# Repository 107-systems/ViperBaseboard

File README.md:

ViperBaseboard
==============

<p align="center">
  
</p>

This repository contains the requirements and the hardware design for MKR Vidor 4000 based Viper quadcopter.

## Quadcopter renderings

## PCB renderings

The **Viper Baseboard** serves as an adapter board between an Arduino MKR Vidor 4000 and various sensors and actuators in order to implement a flight controller for a quadcopter UAV.

The block diagramm has been created using [Ipe](http://ipe.otfried.org/) which can be installed via `sudo apt-get install ipe texlive-full` or `sudo apt-get install ipe texlive-base texlive-latex-recommended` for minimal installation).

## Requirements
### Functional Requirements
#### Rotational/Translational Stabilisation
The quadcopter should be able to stabilise itself against external disturbances concerning its orientation and position with respect to a given setpoint. For determining the current orientation of the quadcopter a suitable Inertial Measurement Unit (IMU) with a suitable sensor fusion algorithm shall be used. For determining translational stabilisation a optical flow sensor consisting of a downward facing camera in combination with a suitable optical flow sensor algorithm shall be used.

#### Vertical (Height) Stabilisation
The quadcopter should be able to hold a set distance over ground. In close proximity to the ground VL53L0X ToF sensors are used to  determine the distance between ground and quadcopter and prevent an accidential crash. When the distance between quadcopter and ground exceeds the maximum measurement range of the ground sensors the height will be controlled using a digital altimeter such as the BMP388.

#### WiFi based Control/Configuration
The quadcopter shall provide a WiFi access point to which a WiFi capable device can connect. Once a WiFi connection is established the quadcopter can be controlled via commands exchanged between quadcopter and device via a network socket. A webserver will run on the quadcopter which allows the user to configure and tweak certain aspects of the quadcopter configuration (e.g. control parameters) or read out quadcopter status.

#### Automonous Landing
The quadcopter should be able to land without user control. Three VL53L0X ToF sensors arranged in a triangle are used to determine the distance between ground and quadcopter and also perform an estimation of the grounds surface.

#### FPV (First-Person-View) Control
The image stream of a forward facing camera (a MIPI connector intented for use with the Omnivision OV5647 camera is available on the MKR VIDOR 4000 board) should be suitably encoded (in the FPGA) and transmitted via WiFi module in such way that a user can be view the image stream e.g. on a mobile phone which allows a FPV control of the quadcopter.\
It should be posible to switch the FPV from forward facing camera to ground facing camera and back. Then the user can choose which camera fits best his needs.

#### SD Card Storage
There should be a socket for a SD card on the baseboard. The flight controller then can log information like position or altitude or store video clips of the cameras or do image generation like map creation with the ground facing camera.

### Sensors
#### VL53L0X
The VL53L0X ToF Sensor allows a measurement range of up to 2 m with a resolution of 1 mm.\
**Attention:** all VL53L0X come up with the same I2C address. So we need additional circuitry to disable them with the XSHUT pin und give them individual addresses one after another.
#### BMP388
The BMP388 is a precision barometric pressure sensor wich relative accuracy of 8 Pascals, which translates to about ± 0.5 meter of altitude.
#### BNO085
The BNO085 contains 3 axis accelerometers, gyroscopes and magnetometers incl. onboard-algorithms for sensor fusion.
#### CD-PA1010D (Optional)
The [CD-PA1010D](doc/datasheet/Sensor-GPS-CD-PA1010D-v-0-3.pdf) is global positioning sensor supporting GPS, GLONASS, GALILEO, QZSS which can be interfaced both via UART and I2C.

### Actuators
#### Zubax Orel 20 ESCs
[Zubax Orel 20](https://kb.zubax.com/display/MAINKB/Zubax+Orel+20) are used as ESC (Electronic Speed Controllers) and controlled via [UAVCAN](https://uavcan.org).

### Electrical Requirements

* **Input Voltage**: 9 - 18.5 V (same as the Zubax Orel 20).
* **Input Protection**: Input voltage should be protected by a TVS diode against voltage spikes from the motors.
There is no fuse because the motor drivers can draw excessive currents. Then a fuse is useless because it should have a very high current rating and then it can'tprotect very much. Additionally the fuse would add additional weight and empose a risk of failure during flight.

#### Power planes and distribution
* **Input Voltage**: to motor drivers and input for voltage regulators, current: 20 to 30 A.
* **5V**:
Input for Arduino because the Arduino doesn't like to be directly fed with 3.3V.
generated on by a switching regulator.
Current: 500 mA + Current for 3.3V devices
* **3.3V**:
for sensors and camera module
generated by the onboard regulator of the Arduino
Current: up to 100 mA, should be OK for the onboard regulator

#### Connectors (mechanical and pinout)
##### Battery / Input
##### CAN
The Zubax Orel 20 ESCs utilize the [JST GH](http://www.jst-mfg.com/product/detail_e.php?series=105) connectors with a pitch of 1.25 mm.

| **Pin** | **Signal** |
|:-------:|:----------:|
| 1       | VCC        |
| 2       | CAN_H      |
| 3       | CAN_L      |
| 4       | GND        |

#### Connections of Arduino MKR Vidor 4000

* **MKR connector** (2.54 mm pinheader, 28 pins)
  * I2C
  * CAN over SPI (like on MKRCANShield)
  * 5V input, 3.3V output
  * RC_IN (for additional remote control receiver)

| **Pin** | **Pin Name** | **Signal**    | **Description**                |
|:-------:|:------------:|:-------------:|:------------------------------:|
| 1       | AREF         | not connected |                                |
| 2       | DAC0/A0      |               |                                |
| 3       | A1           |               |                                |
| 4       | A2           |               |                                |
| 5       | A3           |               |                                |
| 6       | A4           |               |                                |
| 7       | A5           |               |                                |
| 8       | A6           |               |                                |
| 9       | D0           | RC_IN         | remote receiver input          |
| 10      | D1           |               |                                |
| 11      | D2           |               |                                |
| 12      | D3           | MCP2515_CS    | like MKRCANShield              |
| 13      | D4           | SD_CS         | like MKR SD PROTO SHIELD       |
| 14      | D5           |               |                                |
| 15      | D6           |               |                                |
| 16      | D7           | MCP2515_INT   | like MKRCANShield              |
| 17      | D8/MOSI      | MOSI          | MCP2515                        |
| 18      | D9/SCK       | SCK           | MCP2515                        |
| 19      | D10/MISO     | MISO          | MCP2515                        |
| 20      | D11/SDA      | SDA           | I2C for sensors                |
| 21      | D12/SCL      | SCL           | I2C for sensors                |
| 22      | D13/RX       | GPS_RX        | communication with gps module  |
| 23      | D14/TX       | GPS_TX        | communication with gps module  |
| 24      | RESET        | not connected |                                |
| 25      | GND          | GND           |                                |
| 26      | 3V3          | 3V3-rail      | supply voltage for sensors ... |
| 27      | VIN          | 5V            | input from voltage regulator   |
| 28      | 5V           | not connected |                                |

* **USB**: Programming and debugging
* **I2C**: Not used, redundant to MKR connector
* **LiPo**: not used, not suitable
* **MicroHDMI**: not used
* **MiPi Camera Connector**: reserved for front facing camera
* **MiniPCIe Connector**: Connection to OV2640 camera module serving as optical flow sensor. Using VidorCameraAdapter.

### Mechanical Requirements

* **Mounting**: No enclosure planed.
* **Mounting**: There should be mounting holes to mount the baseboard on the [Armattan F1-4B 3MM frame](https://www.armattanquads.com/f1-4b-3mm/)
* **Weight**: The weight should be as low as possible to get better flight performance
* **Cameras**: One camera is mounted on the botom and is facing to the ground. There is an option for a second camera facing forward.

### Environmental Requirements

* **Temperature**: Commercial temperature range should be OK. But parts with industrial range are preferred because of higher reliability.
* **Shock/Vibration**: Care should be taken because of higher vibration on copter therefore no high parts like electrolytic capacitors

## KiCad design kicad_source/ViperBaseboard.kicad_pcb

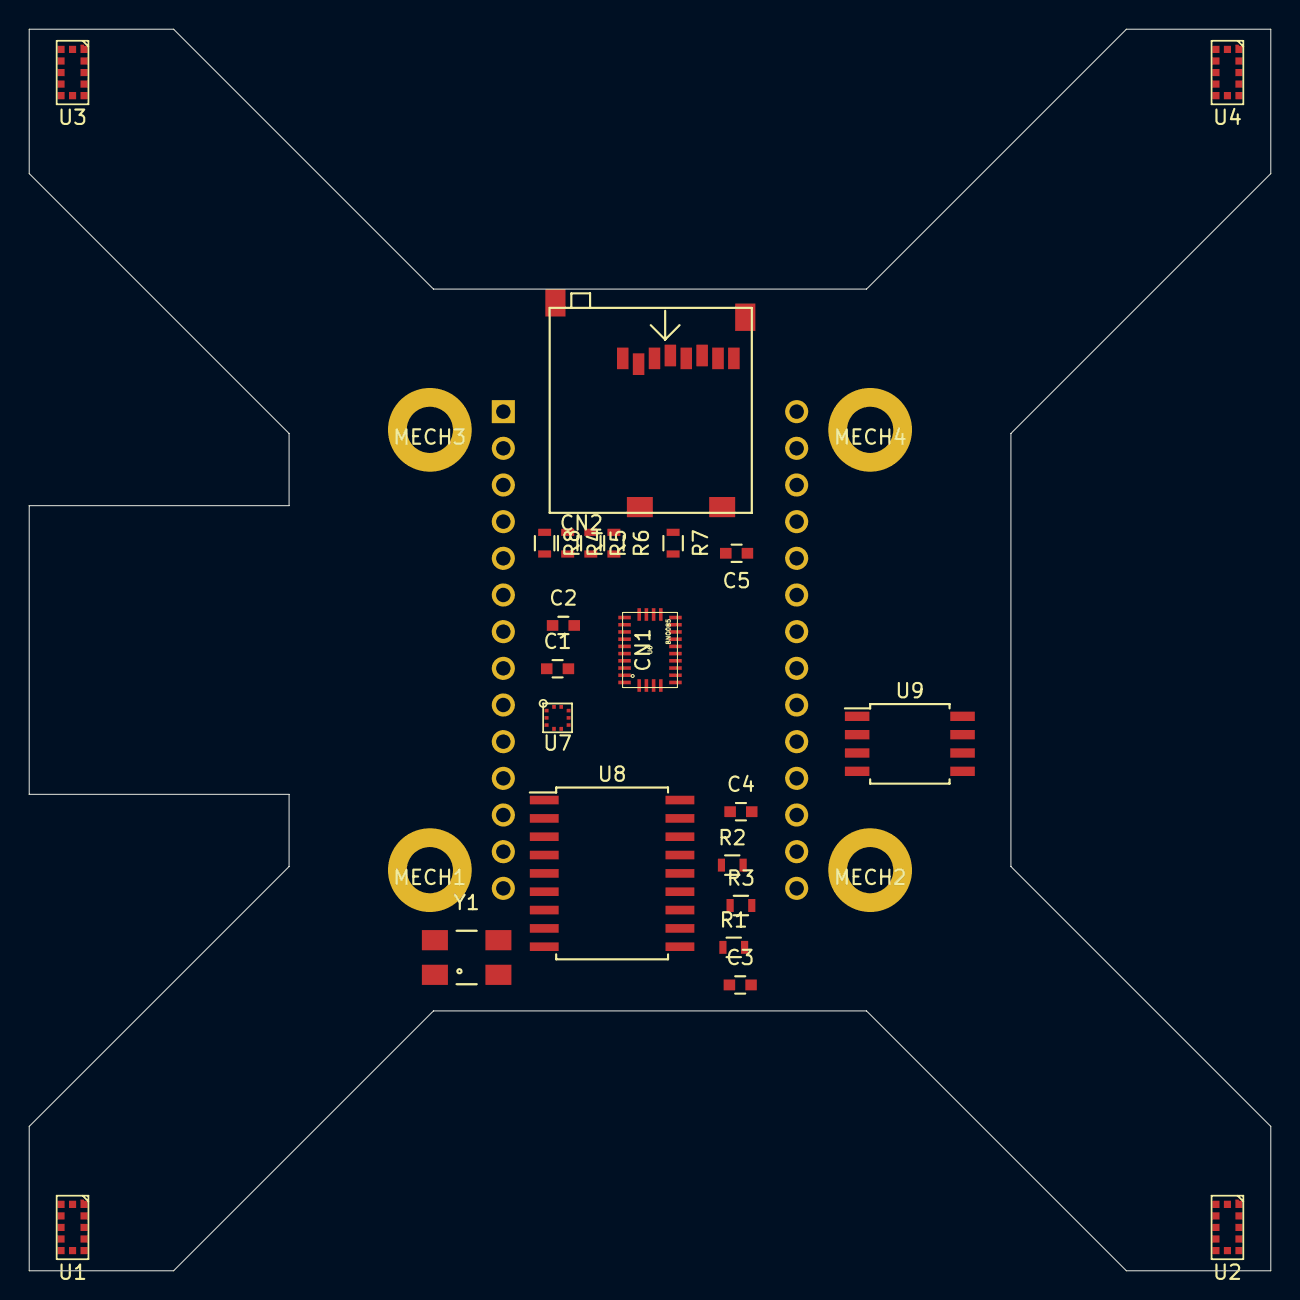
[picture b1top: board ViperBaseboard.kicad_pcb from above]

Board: 2 copper layers, 86.0 x 86.0 mm, 29 parts (1 on the bottom side), 22 nets, no tracks yet.

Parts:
C1, C2, C3, C4: 100nF; C_0603
C5: 100n; C_0603
CN1: ARDUINO_MKR; ARDUINO_MKR_BASEBOARD
CN2: Micro_SDCard; WE_693071010811
MECH1, MECH2, MECH3, MECH4: MHP_3.2_5.8
R1, R2, R3, R8: 10k; R_0603
R4, R5, R6, R7: 100R; R_0603
U1, U2, U3, U4: VL53L0X
U5: ublox_SAM-M8Q
U6: BNO085; LGA-28-5832
U7: BMP388
U8: MCP2515; SOIC-18_7.5x11.6mm_Pitch1.27mm
U9: SN65HVD232; SOIJ-8_5.3x5.3mm_Pitch1.27mm
Y1: 16MHz; Crystal_SMD_0603_4Pads

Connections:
+3V3: C1.1, C2.1, C3.1, C4.1, C5.1, CN1.26, CN2.4, R1.1, R2.1, R3.1, R8.1, U1.1, U1.11, U2.1, U2.11, U3.1, U3.11, U4.1, U4.11, U5.2, U5.17, U6.3, U6.28, U7.1, U7.6, U7.10, U8.18, U9.3
/MCP2515/RXCAN: U8.2, U9.4
/MCP2515/TXCAN: U8.1, U9.1
/SD-Card/SPI_CLK_R: CN2.5, R6.1
/SD-Card/SPI_CS_SD_R: CN2.2, R4.1
/SD-Card/SPI_MISO_R: CN2.7, R7.1
/SD-Card/SPI_MOSI_R: CN2.3, R5.1
/ToF sensors/XSHUT: U1.5, U2.5, U3.5, U4.5
GND: C1.2, C2.2, C3.2, C4.2, C5.2, CN1.25, CN2.6, U1.2, U1.3, U1.4, U1.6, U1.12, U2.2, U2.3, U2.4, U2.6, U2.12, U3.2, U3.3, U3.4, U3.6, U3.12, U4.2, U4.3, U4.4, U4.6, U4.12, U5.1, U5.4, U5.5, U5.6, U5.10, U5.11, U5.15, U5.16, U5.20, U6.2, U6.25, U7.3, U7.5, U7.8, U7.9, U8.9, U9.2, Y1.2, Y1.4
I2C_SCL: CN1.21, U1.10, U2.10, U3.10, U4.10, U6.15, U7.2
I2C_SDA: CN1.20, U1.9, U2.9, U3.9, U4.9, U6.16, U7.4
MCP2515_CS: CN1.12, R2.2, U8.16
MCP2515_INT: CN1.16, R1.2, U8.12
MISO: CN1.19, R7.2, U8.15
MOSI: CN1.17, R5.2, U8.14
unnamed: R3.2, U8.17
unnamed: U8.7, Y1.1
unnamed: U8.8, Y1.3
SCK: CN1.18, R6.2, U8.13
SD_CS: CN1.13, R4.2, R8.2
SER_RX: CN1.22, U5.13
SER_TX: CN1.23, U5.14

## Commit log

2019-12-13 Creating initial block diagram of viper base board
2019-12-13 Adding block diagram to README.
2019-12-16 Specify BMP388 as altimeter and BNO085 as IMU, also adding debug and RC PWM inputs
2019-12-16 Removing PWR block since the need for a power unit for the adapter board is quite obvious
2020-01-07 Adding requirement for autonomous landing
2020-01-09 added mechanical, electrical and environmental requirements
2020-01-09 Adding requirement of rotational/translational stabilisation
2020-01-09 Adding requirement regarding quadcopter control/configuration
2020-01-09 Eliminating VL6180X sensor since its inferior to the VL53L0X After doing some more research I've discovered that the VL53L0X has a measurement range of 0 - 2 m while the VL6180X only have a measureme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
2020-01-12 added comments on power planes, protection and weight
2020-01-13 Adding requirement for vertical (height) stabilisation
    Based on optical ToF when close to ground and air pressure based altimeter when distance to ground exceeds measurement range of ToF sensors.
2020-01-13 Rewriting requirement for autonomous landing since the VL53L0X sensor is already introduced in the section of vertical stabilisation.
2020-01-13 Setting number of ToF sensors from n to 3
2020-01-13 Increase number of ToF sensors to 4 as per agreement in the discussion of PR#1
2020-01-18 added connections of Vidor 4000
2020-01-25 added proposal for pcb stacking
2020-01-27 Adding enumeration of used sensors/actuators.
2020-01-27 Adding FPV control requirement.
2020-01-27 option to switch FPV from forward to ground facing camera
2020-01-27 added requirement for sd card storage
2020-01-27 added hint on I2C adress of VL53L0X
2020-01-27 Adding connector/pinout description for Zubax Orel 20 ESC CAN connector.
2020-02-09 Adding information of the vector grapics software used to create the block diagramm.
2020-02-09 Renaming title of README to be consistent with repository name.
2020-02-09 Refactoring README
2020-02-10 Deleting viper_stackup_20200125.png because it was added in the discussion of PR#1 under https://github.com/107-systems/ViperBaseboard/pull/1#issuecomment-578413592 where it was intented to be used a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
2020-02-12 added table with MKR pinout
2020-02-12 updated block diagramm with new parts and VidorCameraAdapter
2020-02-12 updated IPE install instructions
2020-02-12 Enlarge PNG and fix some formatting issues
2020-02-12 Requirements for Viper Baseboard (#1)
    * Creating initial block diagram of viper base board
    * Adding block diagram to README.
    * Specify BMP388 as altimeter and BNO085 as IMU, also adding debug and RC PWM inputs
    * Removing PWR block since the need for a power unit for the adapter board is quite obvious
    * Adding requirement for autonomous landing
    * added mechanical, electrical and environmental requirements
2020-03-20 Adding suggestion of CD PA1010D GPS sensor to requirements
2020-03-31 added 3D model and rendering of ViperQuadcopter
2020-03-31 added image of rendering of quadcopter
2020-04-02 started pcb schematic and layout
2020-04-02 updated layout, added step of baseboard
2020-04-02 updated 3d model of viperquadcopter with baseboard, generated some screenshots
2020-04-02 updated links to images
2020-04-02 Marking CD-PA1010D GPS sensor as optional - we might select another type (with external antenna)
2020-04-02 CD PA1010D as GPS sensor (#2)
    * Adding suggestion of CD PA1010D GPS sensor to requirements
    * Added 3D model and rendering of ViperQuadcopter
    * Added image of rendering of quadcopter
    * Started pcb schematic and layout
    * Updated layout, added step of baseboard
    * Updated 3d model of viperquadcopter with baseboard, generated some screenshots
2020-04-03 corrected frame size of quadcopter
2020-04-13 updated 3D model with correct dimensions of F1-4B frame
2020-04-13 added motor drivers, props and motors to 3d model
2020-04-13 updated rendering
2020-04-25 redefined shape of PCB
2020-06-03 added BMP388
2020-06-03 added schematic sheet with MCP2515
2020-06-03 added schematic sheet with sd-card
2020-06-03 added renderings of pcb
2020-07-09 Add logo for project viper
2020-10-06 Attempting to restore missing images
2020-11-30 Link to viper logo in .github default repository.
2020-11-30 Removing viper logo file since it was moved into the shared repository
2020-12-01 Update viper logo path.
2020-12-04 Add a CI workflow to sync organization-wide labels
    The workflow will configure the labels of this repository according to the universal labels defined by https://github.com/107-systems/.github/blob/main/universal-repository-labels.json combined with 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
2020-12-15 Reformat pictures for better readability.
2020-12-30 Update viper firmware link.
